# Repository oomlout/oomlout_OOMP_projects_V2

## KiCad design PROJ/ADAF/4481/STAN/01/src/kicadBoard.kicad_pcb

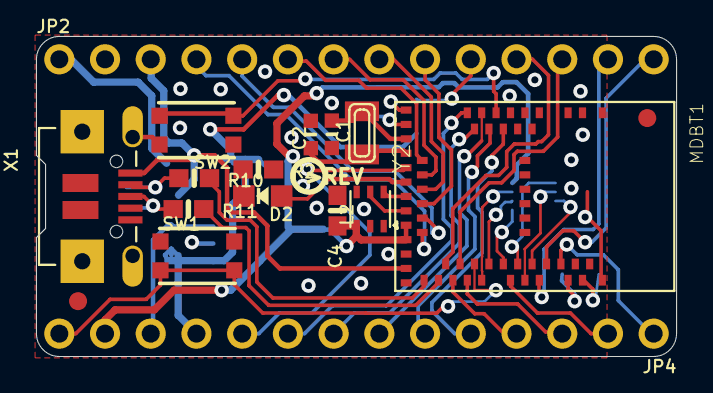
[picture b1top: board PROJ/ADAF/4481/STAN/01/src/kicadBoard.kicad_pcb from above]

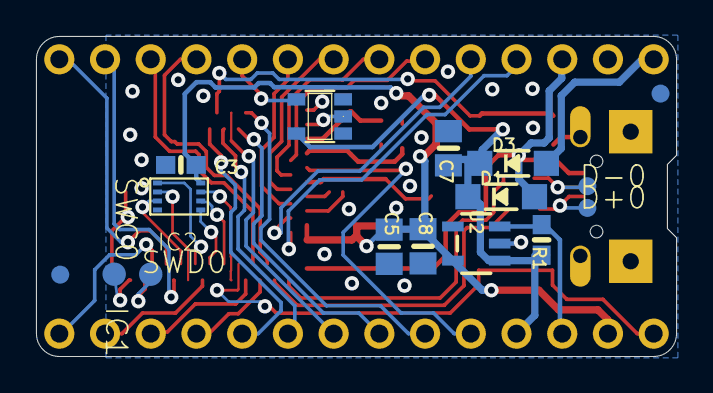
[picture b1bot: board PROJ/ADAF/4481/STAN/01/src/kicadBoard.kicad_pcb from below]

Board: 2 copper layers, 35.6 x 17.8 mm, 36 parts (17 on the bottom side), 48 nets.

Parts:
C1, C2: 22pF; _0603MP
C3, C4: 0.1uF; 0603-NO
C5, C7, C8: 10uF; 0805-NO
D1, D3: MBR120; SOD-123
D2: RED; CHIPLED_0805_NOOUTLINE
D+0: TPTP10R; TP10R
D-0: TPTP10R; TP10R
FID1, FID2, FID3, FID4: FIDUCIAL_1MM
IC1: 74HCT1G125DBV; SOT23-5
IC2: GD25Q16; USON8
JP2, JP4: 1X14_ROUND70
L2: AP102-2020; APA102_2020
MDBT1: MDBT50
R1: 10K; 0603-NO
R2: 1K; 0603-NO
R10, R11: 22; 0603-NO
SW1, SW2: KMR2; BTN_KMR2_4.6X2.8
SWC0: TPTP13R; TP13R
SWD0: TPTP13R; TP13R
U2: AP2112(3.3V); SOT23-5
U$12: ITSYNRF52840_TOP
U$14: ITSYNRF52840_BOT
U$15: PCBFEAT-REV-040
X1: 4u20329; 4UCONN_20329_V2
Y2: 32.768; XTAL3215

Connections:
3.3V: C3.2, C4.2, C5.2, C8.2, IC2.8, JP4.13, L2.3, MDBT1.28, MDBT1.30, U2.5
A0: JP4.10, MDBT1.20
A1: JP4.9, MDBT1.14
A2: JP4.8, MDBT1.13
A3: JP4.7, MDBT1.12
A4: JP4.6, MDBT1.11
A5: JP4.5, MDBT1.9
D2: JP4.1, MDBT1.50
D5: IC1.2, MDBT1.16
D5_5V: IC1.4, JP2.10
D7: JP2.9, MDBT1.25
D9: JP2.8, MDBT1.23
D10: JP2.7, MDBT1.21
D11: JP2.6, MDBT1.19
D12: JP2.5, MDBT1.27
D13: JP2.4, MDBT1.29
D+: D+0.TP, R11.1, X1.D+
D-: D-0.TP, R10.1, X1.D-
DOT_CLK: L2.5, MDBT1.26
DOT_DATA: L2.6, MDBT1.24
EN: JP4.12, R1.1, U2.3
GND: C1.2, C2.2, C3.1, C4.1, C5.1, C7.1, C8.1, IC1.1, IC1.3, IC2.4, JP2.2, L2.4, MDBT1.1, MDBT1.2, MDBT1.15, MDBT1.33, MDBT1.55, R2.2, SW1.A, SW1.A', SW2.A, SW2.A', U2.2, X1.BASE@1, X1.BASE@2, X1.GND, X1.SPRT@1, X1.SPRT@2, X1.SPRT@3, X1.SPRT@4
LED1: D2.A, MDBT1.22
MISO: JP4.2, MDBT1.44
MOSI: JP4.3, MDBT1.39
unnamed: D2.C, R2.1
unnamed: C1.1, MDBT1.17, Y2.P$1
unnamed: C2.1, MDBT1.18, Y2.P$2
QSPI_CS: IC2.1, MDBT1.45
QSPI_DATA0: IC2.5, MDBT1.43
QSPI_DATA1: IC2.2, MDBT1.46
QSPI_DATA2: IC2.3, MDBT1.47
QSPI_DATA3: IC2.7, MDBT1.41
QSPI_SCK: IC2.6, MDBT1.42
RX_D0: JP2.14, MDBT1.49
SCK: JP4.4, MDBT1.37
SCL: JP2.11, MDBT1.36
SDA: JP2.12, MDBT1.38
SWCLK: MDBT1.53, SWC0.TP
SWDIO: MDBT1.51, SWD0.TP
SWITCH: MDBT1.10, SW2.B, SW2.B'
TX_D1: JP2.13, MDBT1.48
USBD+: MDBT1.35, R11.2
USBD-: MDBT1.34, R10.2
VBAT: D3.A, JP2.1
VBUS: D1.A, JP2.3, MDBT1.32, X1.VBUS
VHI: C7.2, D1.C, D3.C, IC1.5, JP4.11, R1.2, U2.1
~RESET: JP4.14, MDBT1.40, SW1.B, SW1.B'

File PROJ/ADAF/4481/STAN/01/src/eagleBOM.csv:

"Part";"Value";"Device";"Package";"Description";"BOM";"POPULARITY";"TP_SIGNAL_NAME";
"C1";"22pF";"CAP_CERAMIC_0603MP";"_0603MP";"Ceramic Capacitors";"";"";"";
"C2";"22pF";"CAP_CERAMIC_0603MP";"_0603MP";"Ceramic Capacitors";"";"";"";
"C3";"0.1uF";"CAP_CERAMIC0603_NO";"0603-NO";"Ceramic Capacitors";"";"";"";
"C4";"0.1uF";"CAP_CERAMIC0603_NO";"0603-NO";"Ceramic Capacitors";"";"";"";
"C5";"10uF";"CAP_CERAMIC0805-NOOUTLINE";"0805-NO";"Ceramic Capacitors";"";"";"";
"C7";"10uF";"CAP_CERAMIC0805-NOOUTLINE";"0805-NO";"Ceramic Capacitors";"";"";"";
"C8";"10uF";"CAP_CERAMIC0805-NOOUTLINE";"0805-NO";"Ceramic Capacitors";"";"";"";
"D+";"TPTP10R";"TPTP10R";"TP10R";"Test pad";"";"3";"";
"D-";"TPTP10R";"TPTP10R";"TP10R";"Test pad";"";"3";"";
"D1";"MBR120";"DIODE-SCHOTTKYSOD-123";"SOD-123";"";"";"";"";
"D2";"RED";"LED0805_NOOUTLINE";"CHIPLED_0805_NOOUTLINE";"LED";"";"";"";
"D3";"MBR120";"DIODE-SCHOTTKYSOD-123";"SOD-123";"";"";"";"";
"FID1";"FIDUCIAL_1MM";"FIDUCIAL_1MM";"FIDUCIAL_1MM";"Fiducial Alignment Points";"EXCLUDE";"";"";
"FID2";"FIDUCIAL_1MM";"FIDUCIAL_1MM";"FIDUCIAL_1MM";"Fiducial Alignment Points";"EXCLUDE";"";"";
"FID3";"FIDUCIAL_1MM";"FIDUCIAL_1MM";"FIDUCIAL_1MM";"Fiducial Alignment Points";"EXCLUDE";"";"";
"FID4";"FIDUCIAL_1MM";"FIDUCIAL_1MM";"FIDUCIAL_1MM";"Fiducial Alignment Points";"EXCLUDE";"";"";
"IC1";"74HCT1G125DBV";"74AHC1G125DBV";"SOT23-5";"Single Bus Buffer Gate with 3-State Output";"";"0";"";
"IC2";"GD25Q16";"SPIFLASH_8PINUX";"USON8";"SOIC8 SPI Flash";"";"";"";
"JP2";"";"HEADER-1X14";"1X14_ROUND70";"";"";"";"";
"JP4";"";"HEADER-1X14";"1X14_ROUND70";"";"";"";"";
"L2";"AP102-2020";"APA1022020";"APA102_2020";"APA102/DotStar Pixels";"";"";"";
"MDBT1";"MDBT50";"MDBT50";"MDBT50";"Raytac Corporation";"";"";"";
"R1";"10K";"RESISTOR_0603_NOOUT";"0603-NO";"Resistors";"";"";"";
"R2";"1K";"RESISTOR_0603_NOOUT";"0603-NO";"Resistors";"";"";"";
"R10";"22";"RESISTOR_0603_NOOUT";"0603-NO";"Resistors";"";"";"";
"R11";"22";"RESISTOR_0603_NOOUT";"0603-NO";"Resistors";"";"";"";
"SW1";"KMR2";"SWITCH_TACT_SMT4.6X2.8";"BTN_KMR2_4.6X2.8";"SMT Tact Switches";"";"";"";
"SW2";"KMR2";"SWITCH_TACT_SMT4.6X2.8";"BTN_KMR2_4.6X2.8";"SMT Tact Switches";"";"";"";
"SWC";"TPTP13R";"TPTP13R";"TP13R";"Test pad";"";"0";"";
"SWD";"TPTP13R";"TPTP13R";"TP13R";"Test pad";"";"0";"";
"U2";"AP2112(3.3V)";"VREG_SOT23-5";"SOT23-5";"SOT23-5 Fixed Voltage Regulators";"";"";"";
"X1";"4u20329";"USB_MICRO_20329_V2";"4UCONN_20329_V2";"USB Connectors";"";"";"";
"Y2";"32.768";"XTAL-3.2X1.5";"XTAL3215";"Low cost SMT crystals, no capacitors included";"";"";"";

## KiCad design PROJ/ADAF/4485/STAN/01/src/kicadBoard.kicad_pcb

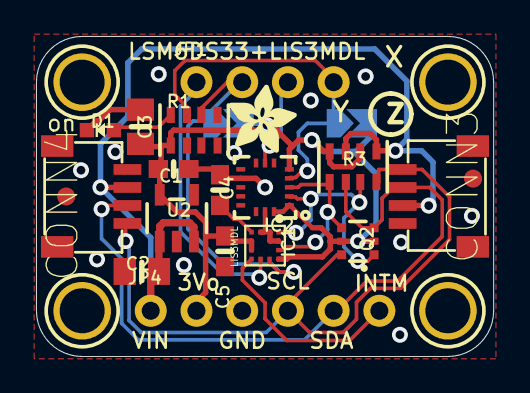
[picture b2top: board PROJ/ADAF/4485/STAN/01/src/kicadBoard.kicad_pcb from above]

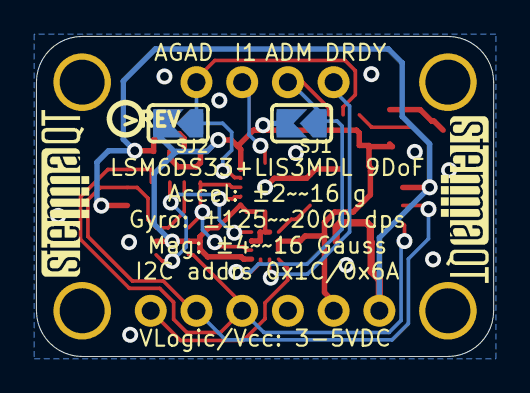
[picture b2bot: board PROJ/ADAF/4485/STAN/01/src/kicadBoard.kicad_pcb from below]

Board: 2 copper layers, 25.4 x 17.8 mm, 28 parts (5 on the bottom side), 14 nets.

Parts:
C1, C4: 0.1uF; 0603-NO
C2, C3: 10uF; 0805-NO
C5: 1uF; 0603-NO
CONN3, CONN4: STEMMA_I2C_QT; JST_SH4
D1: GREEN; CHIPLED_0603_NOOUTLINE
FID3, FID4: FIDUCIAL_1MM
IC1: LIS3MDL; LGA12_2X2MM
IC2: LSM6DS33; LGA16_3X3MM
JP1: 1X04_ROUND
JP4: 1X06_ROUND_70
Q2: BSS138; SOT363
R1, R3: 10K; RESPACK_4X0603
SJ1, SJ2: SOLDERJUMPER_ARROW_NOPASTE
U2: AP2112K-3.3; SOT23-5
U$1, U$17, U$19, U$21: MOUNTINGHOLE2.5; MOUNTINGHOLE_2.5_PLATED
U$20: ADAFRUIT_3.5MM
U$25: PCBFEAT-REV-040
U$30, U$31: STEMMAQT

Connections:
3.3V: C1.1, C3.1, C5.1, IC1.5, IC1.6, IC1.10, IC2.1, IC2.5, IC2.16, JP4.2, Q2.2, Q2.5, R1.1, R3.2, R3.4, SJ1.2, SJ2.2, U2.5
ADAG: IC2.4, JP1.4, R1.7, SJ2.1
ADM: IC1.9, JP1.2, R1.6, SJ1.1
CAP: C4.1, IC1.4
DRDY: IC1.8, JP1.1
GND: C1.2, C2.2, C3.2, C4.2, C5.2, CONN3.1, CONN3.MT1, CONN3.MT2, CONN4.1, CONN4.MT1, CONN4.MT2, D1.C, IC1.2, IC1.3, IC1.12, IC2.8, IC2.9, IC2.10, IC2.11, IC2.12, IC2.13, IC2.15, JP4.3, R1.2, R1.3, U2.2
INT1: IC2.7, JP1.3
INTM: IC1.7, JP4.6
unnamed: D1.A, R1.8
SCL: CONN3.4, CONN4.4, JP4.4, Q2.6, R3.8
SCL_3V: IC1.1, IC2.2, Q2.1, R3.7
SDA: CONN3.3, CONN4.3, JP4.5, Q2.3, R3.6
SDA_3V: IC1.11, IC2.3, Q2.4, R3.5
VCC: C2.1, CONN3.2, CONN4.2, JP4.1, R3.1, R3.3, U2.1, U2.3

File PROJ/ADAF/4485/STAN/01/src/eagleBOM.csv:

"Part";"Value";"Device";"Package";"Description";"BOM";
"C1";"0.1uF";"CAP_CERAMIC0603_NO";"0603-NO";"Ceramic Capacitors";"";
"C2";"10uF";"CAP_CERAMIC0805-NOOUTLINE";"0805-NO";"Ceramic Capacitors";"";
"C3";"10uF";"CAP_CERAMIC0805-NOOUTLINE";"0805-NO";"Ceramic Capacitors";"";
"C4";"0.1uF";"CAP_CERAMIC0603_NO";"0603-NO";"Ceramic Capacitors";"";
"C5";"1uF";"CAP_CERAMIC0603_NO";"0603-NO";"Ceramic Capacitors";"";
"CONN3";"STEMMA_I2C_QT";"STEMMA_I2C_QT";"JST_SH4";"";"";
"CONN4";"STEMMA_I2C_QT";"STEMMA_I2C_QT";"JST_SH4";"";"";
"D1";"GREEN";"LED0603_NOOUTLINE";"CHIPLED_0603_NOOUTLINE";"LED";"";
"FID3";"FIDUCIAL_1MM";"FIDUCIAL_1MM";"FIDUCIAL_1MM";"Fiducial Alignment Points";"EXCLUDE";
"FID4";"FIDUCIAL_1MM";"FIDUCIAL_1MM";"FIDUCIAL_1MM";"Fiducial Alignment Points";"EXCLUDE";
"IC1";"LIS3MDL";"LIS3MDL";"LGA12_2X2MM";"Digital output magnetic sensor. ultra-low-power, high-performance 3-axis magnetometer";"";
"IC2";"LSM6DS33";"LSM6DS33";"LGA16_3X3MM";"";"";
"JP1";"";"HEADER-1X4ROUND";"1X04_ROUND";"PIN HEADER";"";
"JP4";"";"HEADER-1X670MIL";"1X06_ROUND_70";"PIN HEADER";"";
"Q2";"BSS138";"MOSFET-N_DUAL";"SOT363";"Dual N-Channel MOSFET";"";
"R1";"10K";"RESISTOR_4PACK";"RESPACK_4X0603";"Resistor Packs (4 resistors)";"";
"R3";"10K";"RESISTOR_4PACK";"RESPACK_4X0603";"Resistor Packs (4 resistors)";"";
"SJ1";"";"SOLDERJUMPER";"SOLDERJUMPER_ARROW_NOPASTE";"SMD Solder JUMPER";"EXCLUDE";
"SJ2";"";"SOLDERJUMPER";"SOLDERJUMPER_ARROW_NOPASTE";"SMD Solder JUMPER";"EXCLUDE";
"U$1";"MOUNTINGHOLE2.5";"MOUNTINGHOLE2.5";"MOUNTINGHOLE_2.5_PLATED";"Mounting Hole";"EXCLUDE";
"U$17";"MOUNTINGHOLE2.5";"MOUNTINGHOLE2.5";"MOUNTINGHOLE_2.5_PLATED";"Mounting Hole";"EXCLUDE";
"U$19";"MOUNTINGHOLE2.5";"MOUNTINGHOLE2.5";"MOUNTINGHOLE_2.5_PLATED";"Mounting Hole";"EXCLUDE";
"U$21";"MOUNTINGHOLE2.5";"MOUNTINGHOLE2.5";"MOUNTINGHOLE_2.5_PLATED";"Mounting Hole";"EXCLUDE";
"U2";"AP2112K-3.3";"VREG_SOT23-5";"SOT23-5";"SOT23-5 Fixed Voltage Regulators";"";

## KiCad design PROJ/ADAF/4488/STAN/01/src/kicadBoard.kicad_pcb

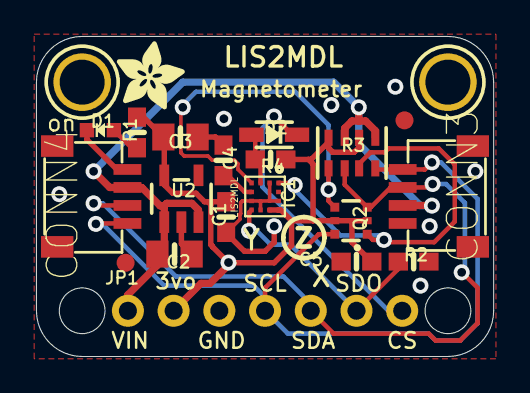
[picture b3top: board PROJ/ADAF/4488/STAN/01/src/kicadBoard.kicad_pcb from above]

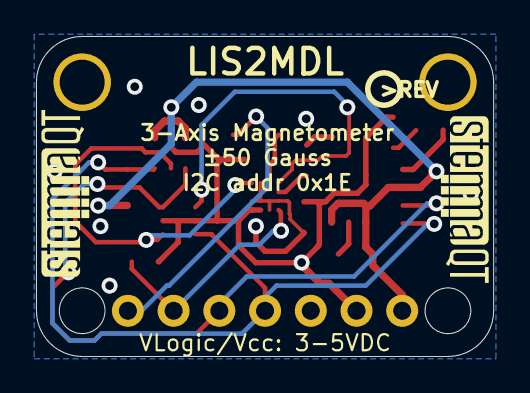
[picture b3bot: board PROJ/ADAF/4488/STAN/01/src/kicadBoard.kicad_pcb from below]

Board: 2 copper layers, 25.4 x 17.8 mm, 27 parts (3 on the bottom side), 12 nets.

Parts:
@HOLE0, @HOLE1: (no value)
C1, C4: 0.1uF; 0603-NO
C2, C3: 10uF; 0805-NO
C5: 1uF; 0603-NO
CONN3, CONN4: STEMMA_I2C_QT; JST_SH4
D1: GREEN; CHIPLED_0603_NOOUTLINE
D2: 1N4148; SOD-323
FID3, FID4: FIDUCIAL_1MM
IC1: LIS2MDL; LGA12_2X2MM
JP1: 1X07_ROUND_70
Q2: BSS138; SOT363
R1, R2, R4: 10K; 0603-NO
R3: 10K; RESPACK_4X0603
U2: AP2112K-3.3; SOT23-5
U$1, U$17: MOUNTINGHOLE2.5; MOUNTINGHOLE_2.5_PLATED
U$11: ADAFRUIT_3.5MM
U$25: PCBFEAT-REV-040
U$30, U$31: STEMMAQT

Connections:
3.3V: C1.1, C3.1, C5.1, IC1.9, IC1.10, JP1.2, Q2.2, Q2.5, R1.1, R3.2, R3.4, R4.2, U2.5
CAP: C4.1, IC1.5
CS: D2.C, JP1.7
CS_3V: D2.A, IC1.3, R4.1
GND: C1.2, C2.2, C3.2, C4.2, C5.2, CONN3.1, CONN3.MT1, CONN3.MT2, CONN4.1, CONN4.MT1, CONN4.MT2, D1.C, IC1.2, IC1.6, IC1.8, IC1.11, IC1.12, JP1.3, R2.1, U2.2
unnamed: D1.A, R1.2
SCL: CONN3.4, CONN4.4, JP1.4, Q2.6, R3.8
SCL_3V: IC1.1, Q2.1, R3.7
SDA: CONN3.3, CONN4.3, JP1.5, Q2.3, R3.6
SDA_3V: IC1.4, Q2.4, R3.5
SDO: IC1.7, JP1.6, R2.2
VCC: C2.1, CONN3.2, CONN4.2, JP1.1, R3.1, R3.3, U2.1, U2.3

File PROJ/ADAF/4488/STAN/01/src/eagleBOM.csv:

"Part";"Value";"Device";"Package";"Description";"BOM";
"C1";"0.1uF";"CAP_CERAMIC0603_NO";"0603-NO";"Ceramic Capacitors";"";
"C2";"10uF";"CAP_CERAMIC0805-NOOUTLINE";"0805-NO";"Ceramic Capacitors";"";
"C3";"10uF";"CAP_CERAMIC0805-NOOUTLINE";"0805-NO";"Ceramic Capacitors";"";
"C4";"0.1uF";"CAP_CERAMIC0603_NO";"0603-NO";"Ceramic Capacitors";"";
"C5";"1uF";"CAP_CERAMIC0603_NO";"0603-NO";"Ceramic Capacitors";"";
"CONN3";"STEMMA_I2C_QT";"STEMMA_I2C_QT";"JST_SH4";"";"";
"CONN4";"STEMMA_I2C_QT";"STEMMA_I2C_QT";"JST_SH4";"";"";
"D1";"GREEN";"LED0603_NOOUTLINE";"CHIPLED_0603_NOOUTLINE";"LED";"";
"D2";"1N4148";"DIODESOD-323";"SOD-323";"Diode";"";
"FID3";"FIDUCIAL_1MM";"FIDUCIAL_1MM";"FIDUCIAL_1MM";"Fiducial Alignment Points";"EXCLUDE";
"FID4";"FIDUCIAL_1MM";"FIDUCIAL_1MM";"FIDUCIAL_1MM";"Fiducial Alignment Points";"EXCLUDE";
"IC1";"LIS2MDL";"LIS2MDL";"LGA12_2X2MM";"";"";
"JP1";"";"HEADER-1X770MIL";"1X07_ROUND_70";"PIN HEADER";"";
"Q2";"BSS138";"MOSFET-N_DUAL";"SOT363";"Dual N-Channel MOSFET";"";
"R1";"10K";"RESISTOR_0603_NOOUT";"0603-NO";"Resistors";"";
"R2";"10K";"RESISTOR_0603_NOOUT";"0603-NO";"Resistors";"";
"R3";"10K";"RESISTOR_4PACK";"RESPACK_4X0603";"Resistor Packs (4 resistors)";"";
"R4";"10K";"RESISTOR_0603_NOOUT";"0603-NO";"Resistors";"";
"U$1";"MOUNTINGHOLE2.5";"MOUNTINGHOLE2.5";"MOUNTINGHOLE_2.5_PLATED";"Mounting Hole";"EXCLUDE";
"U$17";"MOUNTINGHOLE2.5";"MOUNTINGHOLE2.5";"MOUNTINGHOLE_2.5_PLATED";"Mounting Hole";"EXCLUDE";
"U2";"AP2112K-3.3";"VREG_SOT23-5";"SOT23-5";"SOT23-5 Fixed Voltage Regulators";"";

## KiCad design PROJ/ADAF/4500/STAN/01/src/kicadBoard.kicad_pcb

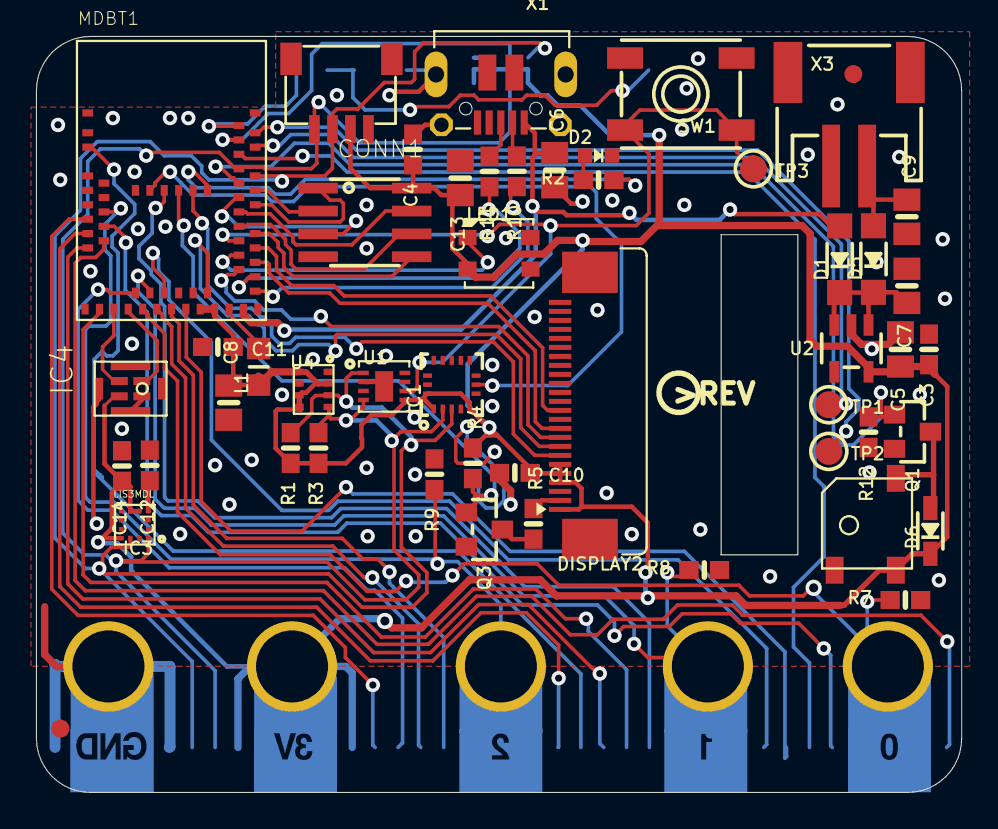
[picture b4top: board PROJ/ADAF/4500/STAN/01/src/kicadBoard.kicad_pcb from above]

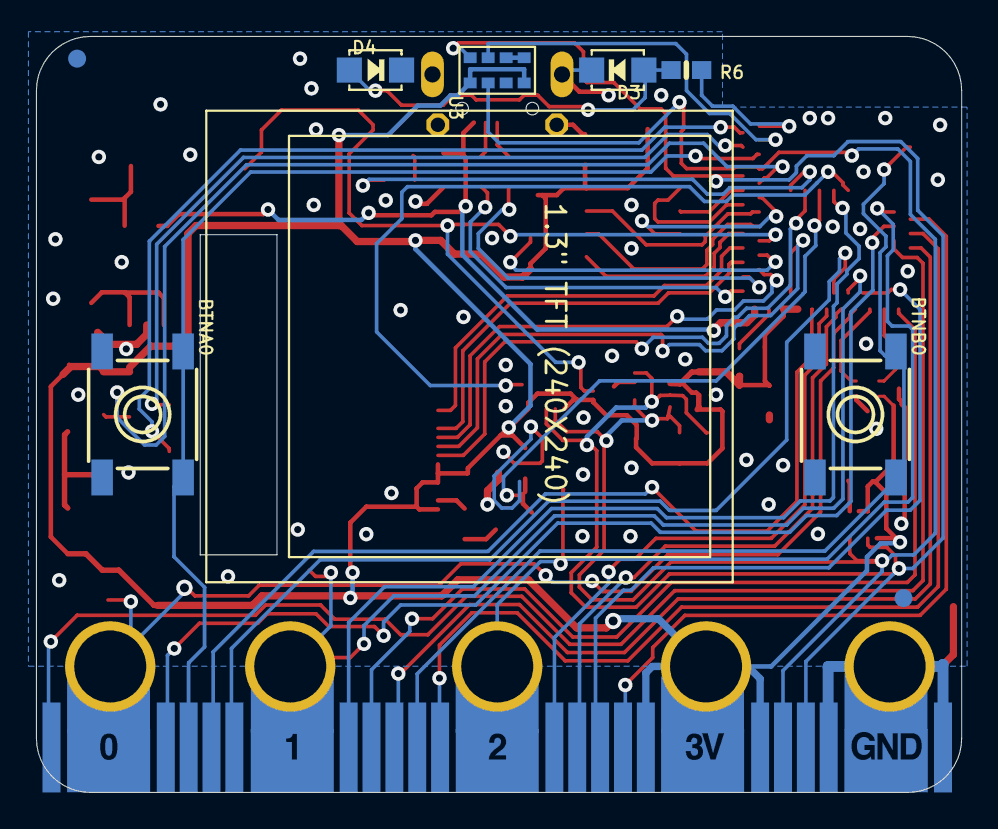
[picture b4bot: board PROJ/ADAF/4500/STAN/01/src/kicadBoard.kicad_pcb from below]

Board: 2 copper layers, 51.4 x 42.0 mm, 62 parts (10 on the bottom side), 59 nets.

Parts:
BTNA0: 6mm; 6MMX6MM_TACTILE_SMT
BTNB0: 6mm; 6MMX6MM_TACTILE_SMT
C3, C4, C10, C11, C12, C14: 0.1uF; 0603-NO
C5, C6, C7, C8, C9, C13: 10uF; 0805-NO
CONN1: STEMMA_I2C_QT; JST_SH4
D1, D5: MBR120; SOD-123
D2: RED; CHIPLED_0603_NOOUTLINE
D3, D4: L130-5780001400001; EVERLIGHT_45-21
D6: 1N4148; SOD-323
DISPLAY2: DISP_LCD_ST7789_1.3IN; TFT_1.3IN_240X240_24P
FID1, FID2, FID3, FID4: FIDUCIAL_1MM
IC1: LSM6DS33; LGA16_3X3MM
IC2: GD25Q16; SOIC8_150MIL
IC3: LIS3MDL; LGA12_2X2MM
IC4: MIC_PDM; SPK0415HM4H
L1: DNP; _0805MP
LED1: WS2812B3535; LED3535
MB1: MICRO:BIT_EDGE; MICROBIT_EDGE
MDBT1: MDBT50
Q1, Q3: BSS138; SOT23-WIDE
R1, R3: 4.7K; 0603-NO
R2: 1K; 0603-NO
R4, R12: 10K; 0603-NO
R5, R6: 10; 0603-NO
R7, R8, R9: 1Mohm; 0603-NO
R10, R11: 22; 0603-NO
SP1: SPEAKER_BUZZER5MM; BUZZER_SMT_5MM
SW1: KMR2; EVQ-Q2_SMALLER
TP1, TP2, TP3: TESTPOINT_ROUND_1.5MM
U1: SHT30; SHT3X
U2: AP2112(3.3V); SOT23-5
U3: APDS-9960
U4: BMP280
U$10: PCBFEAT-REV-056
U$37: CLUE_BACK
U$52: CLUE_FRONT
X1: 4u20329; 4UCONN_20329_SLIM
X3: JSTPH; JSTPH2

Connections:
3.3V: C3.2, C4.2, C5.2, C8.2, C10.2, C11.2, C13.2, C14.2, CONN1.2, D6.C, DISPLAY2.1, DISPLAY2.4, DISPLAY2.5, DISPLAY2.6, IC1.1, IC1.5, IC1.16, IC2.8, IC3.5, IC3.6, IC3.10, IC4.1, L1.1, LED1.2, MB1.+3V3, MB1.+3V3@1, MB1.+3V3@2, MDBT1.28, MDBT1.30, R1.2, R3.2, R4.2, SP1.+, U1.5, U2.5, U3.5, U3.8, U4.2, U4.5, U4.6, U4.8
APDS_IRQ: MDBT1.52, U3.2
BACKLIGHT: MDBT1.59, Q3.1, R4.1
CAP1: C12.2, IC3.4
D0/AIN2: MB1.P0, MDBT1.20, R7.2
D1/AIN3: MB1.P1, MDBT1.21, R8.2
D2/AIN4: MB1.P2, MDBT1.9, R9.2
D3/AIN5: MB1.P3, MDBT1.13
D4/AIN6: MB1.P4, MDBT1.11
D5/BUTTON_A: BTNA0.B, BTNA0.B', MB1.P5, MDBT1.50
D6: MB1.P6, MDBT1.26
D7: MB1.P7, MDBT1.23
D8: MB1.P8, MDBT1.58
D9: MB1.P9, MDBT1.16
D10/AIN7: MB1.P10, MDBT1.14
D11/BUTTON_B: BTNB0.B, BTNB0.B', MB1.P11, MDBT1.3
D12/AIN0: MB1.P12, MDBT1.12
D13/SCK: MB1.P13, MDBT1.24
D14/MISO: MB1.P14, MDBT1.22
D15/MOSI: MB1.P15, MDBT1.19
D16/AIN1: MB1.P16, MDBT1.10
D19/SCL: CONN1.4, IC1.2, IC3.1, MB1.P19, MDBT1.49, R3.1, U1.4, U3.7, U4.4
D20/SDA: CONN1.3, IC1.3, IC3.11, MB1.P20, MDBT1.48, R1.1, U1.1, U3.1, U4.3
D+: R11.1, X1.D+
D-: R10.1, X1.D-
DCCH: L1.2, MDBT1.31
GND: BTNA0.A, BTNA0.A', BTNB0.A, BTNB0.A', C3.1, C4.1, C5.1, C6.1, C7.1, C8.1, C9.1, C10.1, C11.1, C12.1, C13.1, C14.1, CONN1.1, CONN1.MT1, CONN1.MT2, D2.C, D3.K, D4.K, DISPLAY2.3, DISPLAY2.11, DISPLAY2.13, DISPLAY2.14, DISPLAY2.15, DISPLAY2.16, DISPLAY2.17, DISPLAY2.18, DISPLAY2.19, DISPLAY2.20, DISPLAY2.23, DISPLAY2.24, IC1.4, IC1.8, IC1.9, IC1.10, IC1.11, IC1.12, IC1.13, IC1.15, IC2.4, IC3.2, IC3.3, IC3.9, IC3.12, IC4.2, IC4.5, IC4.6, IC4.7, IC4.8, LED1.4, MB1.GND, MB1.GND@1, MB1.GND@2, MDBT1.1, MDBT1.2, MDBT1.15, MDBT1.33, MDBT1.55, Q1.2, Q3.2, R7.1, R8.1, R9.1, R12.2, SW1.A, SW1.A', U1.2, U1.7, U1.8, U1.THERMAL, U2.2, U3.6, U4.1, U4.7, X1.BASE@1, X1.BASE@2, X1.GND, X1.SPRT@1, X1.SPRT@2, X1.SPRT@3, X1.SPRT@4, X3.1
LED1: MDBT1.61, R2.1
LEDK: DISPLAY2.2, R5.2
LSM_IRQ: IC1.7, MDBT1.57
unnamed: Q3.3, R5.1
unnamed: U3.3, U3.4
unnamed: D3.A, D4.A, R6.1
unnamed: D6.A, Q1.3, SP1.-
unnamed: D2.A, R2.2
NEOPIX: LED1.1, MDBT1.38
PDM_CLK: IC4.3, MDBT1.18
PDM_DAT: IC4.4, MDBT1.17
QSPI_CS: IC2.1, MDBT1.44
QSPI_DATA0: IC2.5, MDBT1.41
QSPI_DATA1: IC2.2, MDBT1.46
QSPI_DATA2: IC2.3, MDBT1.45
QSPI_DATA3: IC2.7, MDBT1.43
QSPI_SCK: IC2.6, MDBT1.42
RESET: MDBT1.40, SW1.B, SW1.B', TP3.P$1, U1.6
SPKR: MDBT1.47, Q1.1, R12.1
SWCLK: MDBT1.53, TP2.P$1
SWDIO: MDBT1.51, TP1.P$1
TFT_CS: DISPLAY2.8, MDBT1.29
TFT_DC: DISPLAY2.10, MDBT1.37
TFT_MOSI: DISPLAY2.12, MDBT1.39
TFT_RESET: DISPLAY2.7, MDBT1.60
TFT_SCK: DISPLAY2.9, MDBT1.36
USBD+: MDBT1.35, R11.2
USBD-: MDBT1.34, R10.2
VBAT: C9.2, D5.A, X3.2
VBUS: C6.2, D1.A, MDBT1.32, X1.VBUS
VHI: C7.2, D1.C, D5.C, U2.1, U2.3
WHITE_LED: MDBT1.54, R6.2

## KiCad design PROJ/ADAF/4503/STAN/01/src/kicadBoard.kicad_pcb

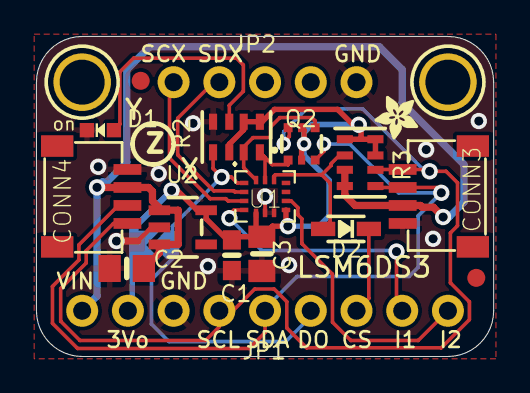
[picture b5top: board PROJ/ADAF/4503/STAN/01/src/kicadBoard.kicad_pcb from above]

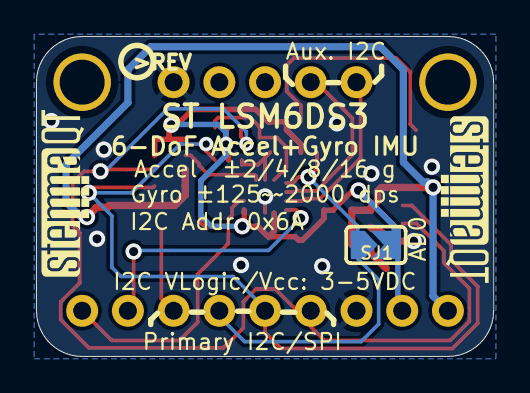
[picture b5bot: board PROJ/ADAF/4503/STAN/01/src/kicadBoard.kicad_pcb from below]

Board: 2 copper layers, 25.4 x 17.8 mm, 23 parts (4 on the bottom side), 15 nets.

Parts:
C1: 0.1uF; 0603-NO
C2, C3: 10uF; 0805-NO
CONN3, CONN4: STEMMA_I2C_QT; JST_SH4
D1: GREEN; CHIPLED_0603_NOOUTLINE
D2: 1N4148; SOD-323
FID3, FID4: FIDUCIAL_1MM
JP1: 1X09_ROUND_70
JP2: 1X05_ROUND_70
Q2: BSS138; SOT363
R2, R3: 10K; RESPACK_4X0603
SJ1: SOLDERJUMPER_ARROW_NOPASTE
U1: LSM6DS3; LGA-14L
U2: AP2112K-3.3; SOT23-5
U$1, U$17: MOUNTINGHOLE2.5; MOUNTINGHOLE_2.5_PLATED
U$9: ADAFRUIT_2.5MM
U$25: PCBFEAT-REV-040
U$30, U$31: STEMMAQT

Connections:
3.3V: C1.1, C3.1, JP1.2, Q2.2, Q2.5, R2.1, R2.2, R2.6, R3.3, R3.4, R3.5, SJ1.2, U1.5, U1.8, U2.5
CS_3V: D2.A, R3.6, U1.12
CS_5V: D2.C, JP1.7
GND: C1.2, C2.2, C3.2, CONN3.1, CONN4.1, D1.C, JP1.3, JP2.1, R2.4, U1.6, U1.7, U2.2
INT1: JP1.8, U1.4
INT2: JP1.9, U1.9
unnamed: D1.A, R2.3
SCL: CONN3.4, CONN4.4, JP1.4, Q2.6, R3.2
SCL_3V: Q2.1, R2.8, U1.13
SCX: JP2.5, U1.3
SDA: CONN3.3, CONN4.3, JP1.5, Q2.3, R3.1
SDA_3V: Q2.4, R2.7, U1.14
SDO: JP1.6, R2.5, SJ1.1, U1.1
SDX: JP2.4, U1.2
VCC: C2.1, CONN3.2, CONN4.2, JP1.1, R3.7, R3.8, U2.1, U2.3

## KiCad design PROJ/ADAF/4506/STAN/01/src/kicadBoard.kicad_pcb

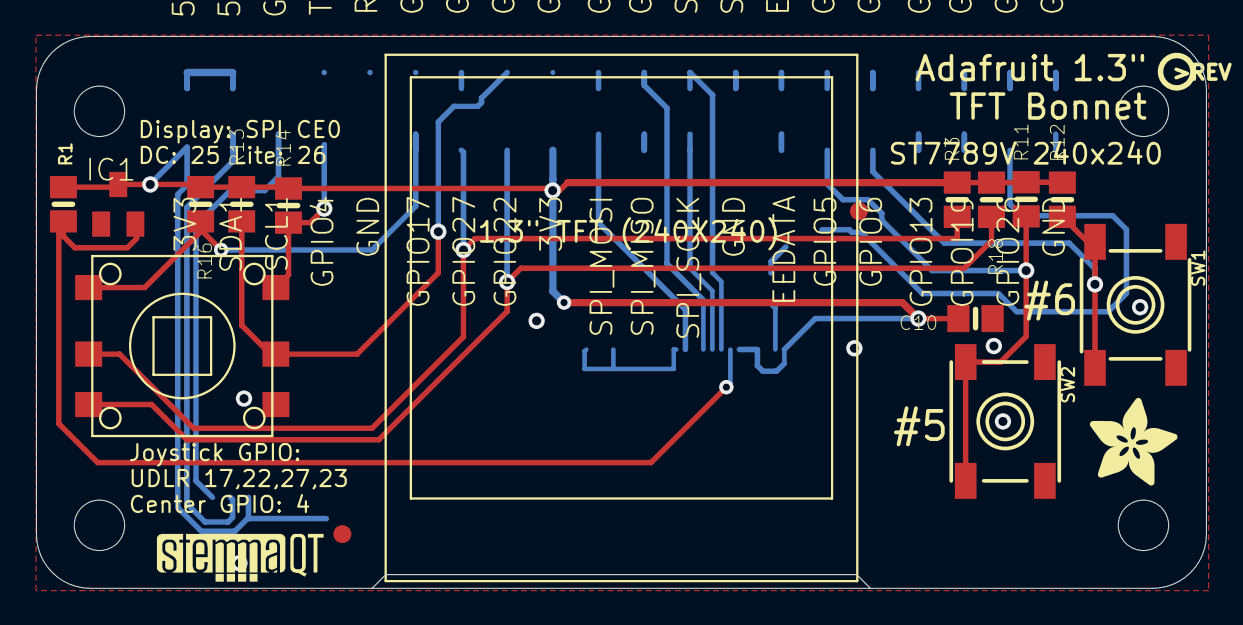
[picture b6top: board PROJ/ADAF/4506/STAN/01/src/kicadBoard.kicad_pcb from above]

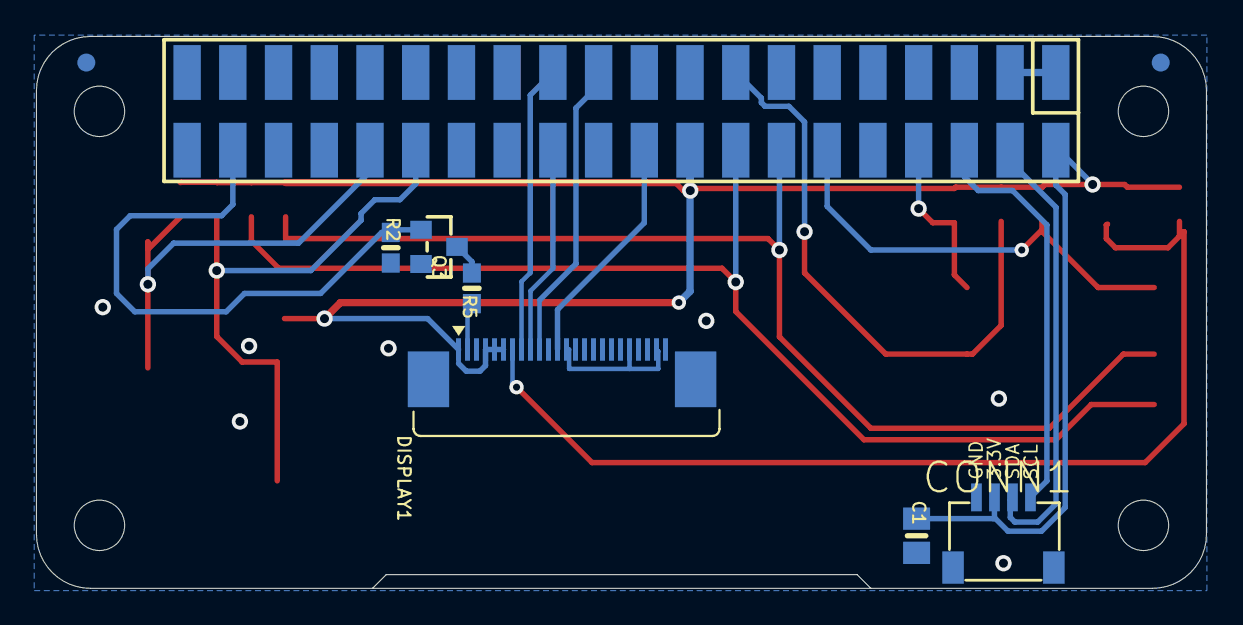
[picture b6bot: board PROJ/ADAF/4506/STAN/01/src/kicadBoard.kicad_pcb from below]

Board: 2 copper layers, 65.0 x 30.7 mm, 25 parts (6 on the bottom side), 20 nets.

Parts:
C1, C10: 10uF; 0805-NO
CONN1: STEMMA_I2C_QT; JST_SH4
DISPLAY1: DISP_LCD_ST7789_1.3IN; TFT_1.3IN_240X240_24P
FID1, FID2: FIDUCIAL_1MM
IC1: APX803; SOT23
Q3: BSS138; SOT23-WIDE
R1, R3, R11, R12, R13, R14, R16, R18: 10K; 0805-NO
R2: 10K; 0603-NO
R5: 10; 0603-NO
RPI1: RASPBERRYPI_BPLUS_BONNETSMT; PI_BONNET_SMT
SW1: EVQQ; 6MMX6MM_TACTILE_SMT
SW2: EVQQ; 6MM_SMT
SW3: NAVSWITCHSKQUABAUE010; SKQUBAE010
U$2: PCBFEAT-REV-040
U$28: ADAFRUIT_5MM
U$29: STEMMAQT

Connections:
3.3V: C1.2, C10.2, CONN1.2, DISPLAY1.1, DISPLAY1.4, DISPLAY1.5, DISPLAY1.6, IC1.3, R1.2, R3.2, R11.2, R12.2, R13.2, R14.2, R16.1, R18.1, RPI1.1, RPI1.17
5.0V: RPI1.2, RPI1.4
GND: C1.1, C10.1, CONN1.1, DISPLAY1.3, DISPLAY1.11, DISPLAY1.13, DISPLAY1.14, DISPLAY1.15, DISPLAY1.16, DISPLAY1.17, DISPLAY1.18, DISPLAY1.19, DISPLAY1.20, DISPLAY1.23, DISPLAY1.24, IC1.1, Q3.2, R2.1, RPI1.6, RPI1.9, RPI1.14, RPI1.20, RPI1.25, RPI1.30, RPI1.34, RPI1.39, SW1.B, SW1.B', SW2.B, SW2.B', SW3.4
GPIO4: R14.1, RPI1.7, SW3.6
GPIO5: R11.1, RPI1.29, SW2.A, SW2.A'
GPIO6: R12.1, RPI1.31, SW1.A, SW1.A'
GPIO17: R16.2, RPI1.11, SW3.1
GPIO22: R18.2, RPI1.15, SW3.3
GPIO23: R13.1, RPI1.16, SW3.5
GPIO27: R3.1, RPI1.13, SW3.2
LEDK: DISPLAY1.2, R5.2
MOSI: DISPLAY1.12, RPI1.19
unnamed: Q3.3, R5.1
SCL: CONN1.4, RPI1.5
SCLK: DISPLAY1.9, RPI1.23
SDA: CONN1.3, RPI1.3
TFT_CS: DISPLAY1.8, RPI1.24
TFT_DC: DISPLAY1.10, RPI1.22
TFT_LITE: Q3.1, R2.2, RPI1.37
TFT_RST: DISPLAY1.7, IC1.2, R1.1

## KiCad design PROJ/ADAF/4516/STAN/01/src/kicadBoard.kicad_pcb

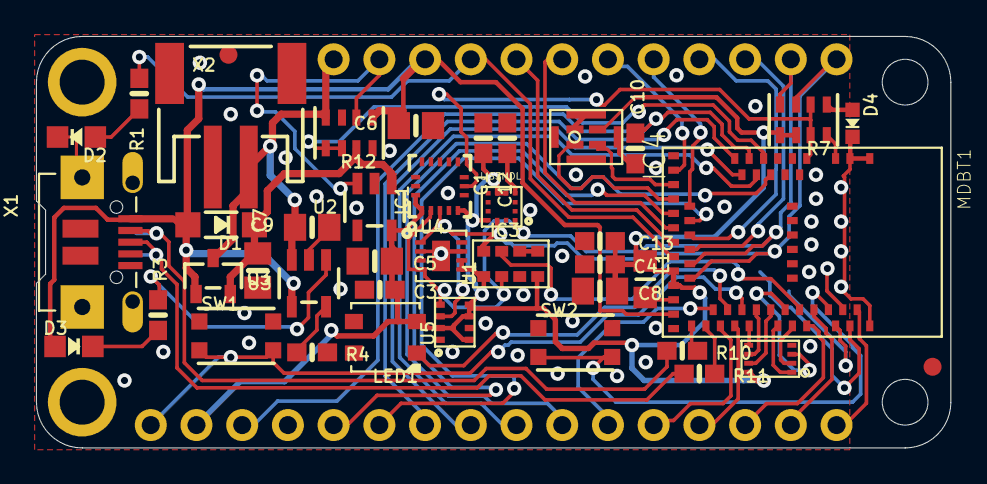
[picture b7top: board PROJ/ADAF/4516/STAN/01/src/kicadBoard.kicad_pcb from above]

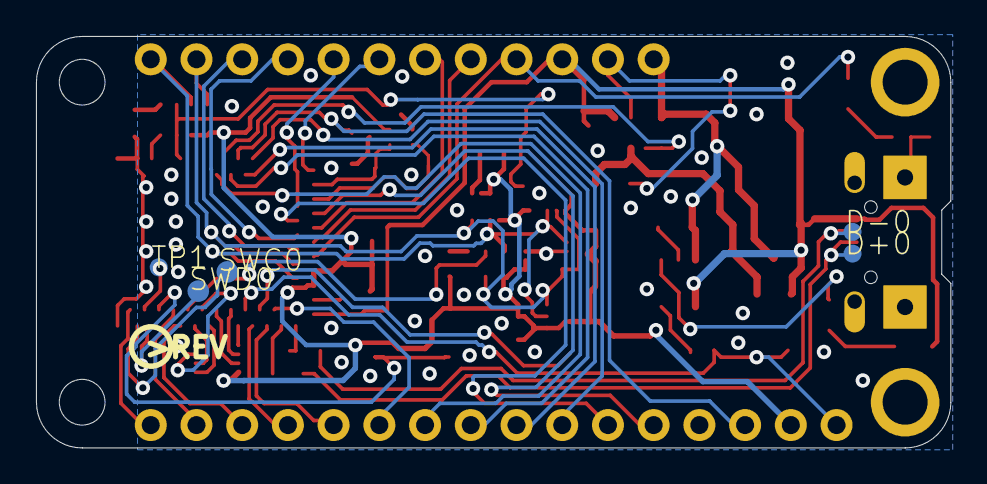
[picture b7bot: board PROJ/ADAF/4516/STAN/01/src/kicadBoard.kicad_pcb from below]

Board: 4 copper layers, 50.8 x 22.9 mm, 50 parts (7 on the bottom side), 58 nets.

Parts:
C1, C3, C10, C12, C13: 0.1uF; 0603-NO
C4: 1uF; 0603-NO
C5, C6, C7, C8, C9: 10uF; 0805-NO
D1: MBR054; SOD-123
D2: RED; CHIPLED_0805_NOOUTLINE
D3: ORANGE; CHIPLED_0805_NOOUTLINE
D4: BLUE; CHIPLED_0603_NOOUTLINE
D+0: TPTP10R; TP10R
D-0: TPTP10R; TP10R
FID1, FID2: FIDUCIAL_1MM
IC1: LSM6DS33; LGA16_3X3MM
IC2: GD25Q16; USON8
IC3: LIS3MDL; LGA12_2X2MM
IC4: MIC_PDM; SPK0415HM4H
L1: DNP; _0805MP
LED1: WS2812B3535; LED3535
MDBT1: MDBT50
MS1: FEATHERWING_NODIM
Q3: DMG2305; SOT23-R
R1: 2.2K; 0603-NO
R3: 1K; 0603-NO
R4: 4.7K; 0603-NO
R7: 4.7K; RESPACK_4X0603
R10, R11: 22; 0603-NO
R12: 100K; RESPACK_4X0603
SW1, SW2: KMR2; BTN_KMR2_4.6X2.8
SWC0: TPTP12R; TP12R
SWD0: TPTP12R; TP12R
TP1: TPTP10R; TP10R
U1: APDS-9960
U2: AP2112(3.3V); SOT23-5
U3: MCP73831T-2ACI/OT; SOT23-5
U4: SHT30; SHT3X
U5: BMP280
U$10: PCBFEAT-REV-056
U$14: FEATHERSENSE_TOP
U$75: FEATHERSENSE_BOT
X1: 4u20329; 4UCONN_20329_V2
X2: CON_JST_PH_2PIN_MTPH2; JSTPH2

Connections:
3.3V: C1.2, C3.2, C4.2, C5.2, C8.2, C13.2, IC1.1, IC1.5, IC1.16, IC2.8, IC3.5, IC3.6, IC3.10, IC4.1, L1.1, LED1.2, MDBT1.28, MDBT1.30, MS1.2, R7.5, R7.6, U1.5, U1.8, U2.5, U4.5, U4.6, U5.2, U5.5, U5.6, U5.8
A0: MDBT1.20, MS1.5
A1: MDBT1.21, MS1.6
A2: MDBT1.14, MS1.7
A3: MDBT1.13, MS1.8
A4: MDBT1.11, MS1.9
A5: MDBT1.9, MS1.10
APDS_IRQ: MDBT1.47, U1.2
AREF: C10.2, MDBT1.12, MS1.3
CAP1: C12.2, IC3.4
D2: MDBT1.54, MS1.16
D3: IC1.7, MDBT1.4, R7.2, R7.7
D5: MDBT1.25, MS1.19
D6: MDBT1.23, MS1.20
D9: MDBT1.19, MS1.21
D10: MDBT1.16, MS1.22
D11: MDBT1.22, MS1.23
D12: MDBT1.24, MS1.24
D13: MDBT1.26, MS1.25, R1.1
D+: D+0.TP, R11.1, X1.D+
D-: D-0.TP, R10.1, X1.D-
DCCH: L1.2, MDBT1.31
EN: MS1.27, R12.2, U2.3
GND: C1.1, C3.1, C4.1, C5.1, C6.1, C7.1, C8.1, C9.1, C10.1, C12.1, C13.1, D2.C, D4.C, IC1.4, IC1.8, IC1.9, IC1.10, IC1.11, IC1.12, IC1.13, IC1.15, IC2.4, IC3.2, IC3.3, IC3.9, IC3.12, IC4.2, IC4.5, IC4.6, IC4.7, IC4.8, LED1.4, MDBT1.1, MDBT1.2, MDBT1.15, MDBT1.33, MDBT1.55, MS1.4, R4.2, R12.3, R12.8, SW1.A, SW1.A', SW2.A, SW2.A', U1.6, U2.2, U3.2, U4.2, U4.7, U4.8, U4.THERMAL, U5.1, U5.7, X1.BASE@1, X1.BASE@2, X1.GND, X1.SPRT@1, X1.SPRT@2, X1.SPRT@3, X1.SPRT@4, X2.1, X2.NC1, X2.NC2
LED2: MDBT1.3, R7.8
MISO: MDBT1.39, MS1.13
MOSI: MDBT1.37, MS1.12
unnamed: D3.C, R3.1
unnamed: U1.3, U1.4
unnamed: D4.A, R7.1
unnamed: D2.A, R1.2
unnamed: R3.2, U3.1
unnamed: R4.1, U3.5
NEOPIX: LED1.1, MDBT1.38
NFC2: MDBT1.52, TP1.TP
PDM_CLK: IC4.3, MDBT1.18
PDM_DAT: IC4.4, MDBT1.17
QSPI_CS: IC2.1, MDBT1.44
QSPI_DATA0: IC2.5, MDBT1.41
QSPI_DATA1: IC2.2, MDBT1.46
QSPI_DATA2: IC2.3, MDBT1.45
QSPI_DATA3: IC2.7, MDBT1.43
QSPI_SCK: IC2.6, MDBT1.42
RESET: MDBT1.40, MS1.1, SW1.B, SW1.B'
RXD: MDBT1.48, MS1.14
SCK: MDBT1.36, MS1.11
SCL: IC1.2, IC3.1, MDBT1.27, MS1.18, R7.4, U1.7, U4.4, U5.4
SDA: IC1.3, IC3.11, MDBT1.29, MS1.17, R7.3, U1.1, U4.1, U5.3
SWCLK: MDBT1.53, SWC0.TP
SWDIO: MDBT1.51, SWD0.TP
SWITCH: MDBT1.50, SW2.B, SW2.B'
TXD: MDBT1.49, MS1.15
USBD+: MDBT1.35, R11.2
USBD-: MDBT1.34, R10.2
VBAT: C9.2, MS1.28, Q3.3, R12.4, U3.3, X2.2
VBUS: C6.2, D1.A, D3.A, MDBT1.32, MS1.26, Q3.1, R12.1, U3.4, X1.VBUS
VDIV: MDBT1.10, R12.5, R12.6
VHI: C7.2, D1.C, Q3.2, R12.7, U2.1
